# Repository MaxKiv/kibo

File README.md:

# The KiBo splitboard

An awesome custom split keyboard, at least I think so 😉. Made by Max Kivits and
Timon Borg, the KiBo!

This keyboard is loosely based on the [Piantor] and [Cantor] keyboards. It's a
42-key diodeless non-flippable cherry-mx hotswapable mechanical split keyboard
with aggressive column staggering. It's powered by 2 RP2040, completely overkill!
I redesigned the PCB to use cherry-mx style hotswap switches and adjusted the
margins so it fits my hands better.
The pcb features an artsy silklayer, because why not?

The casing is designed by Timon Borg, a god amongst fusion360 users!

KiBo uses the amazing [qmk] firmware to become a keyboard.

## Features

* RP2040 MCU - A low-cost, easy-to-source, powerful microcontroller with dual Arm Cortex-M0+ @ 133MHz, 264kB on-chip SRAM and 2MB (up to 16MB, depending on the breakout board) off-chip external flash memory. You can enable a lot of features and layers. Never worry about the firmware size limit.
* Cantor layout - Ergonomic strong column staggering for short pinkies.
* Non-flippable PCBs - Fewer ways to make mistakes when you install the controller breakout boards. Great for first time keyboard builders.
* Diodeless - A more robust build with fewer things to solder or break.
* Hybrid hotswap and soldered-in low profile choc switches - Experiment with different key switches with the hotswap sockets, or solder the key switches for a more stable build.
* Breakable pinky column - Easily convert the PCB from a 42-key to 36-key layout. You can snap off the pinky column without specialized tools.

## Bill of Materials (BOM)

Quantity | Item | Notes
--- | --- | ---
1 | KiBo PCB (Left)
1 | KiBo PCB (Right)
2 | RP2040 breakout boards (such as Raspberry Pi Pico or WeAct RP2040)
42 (or 36) | cherry-mx style switches of your favorite flavor
42 (or 36) | cherry-mx style keycaps of your favorite variety
2 | TRRS jack (PJ-320A)
1 | 3.5mm TRRS cable | TRS cable cannot be used
42 (or 36) | cherry-mx style hotswap sockets | Optional, you can solder the switches directly if you do not use hotswap sockets
4 | Pin headers (20p) or sockets  | Only required for boards without castellated holes
2 | 10kΩ 1206 (3216M) SMD resistor | Only required if you do not want to use SPLIT_USB DETECT, and for boards without a built in VBUS_SENSE circuit
2 | 5.6kΩ 1206 (3216M) SMD resistor | Only required if you do not want to use SPLIT_USB DETECT, and for boards without a built in VBUS_SENSE circuit
1 | KiBo Case (Left) | 3D print your own
1 | KiBo Case (Right)| 3D print your own

* Note: Raspberry Pi Pico comes with castellated holes and a built in VBUS_SENSE circuit

[Piantor]: https://github.com/beekeeb/piantor
[Cantor]: https://github.com/diepala/cantor
[qmk]: https://github.com/qmk/qmk_firmware

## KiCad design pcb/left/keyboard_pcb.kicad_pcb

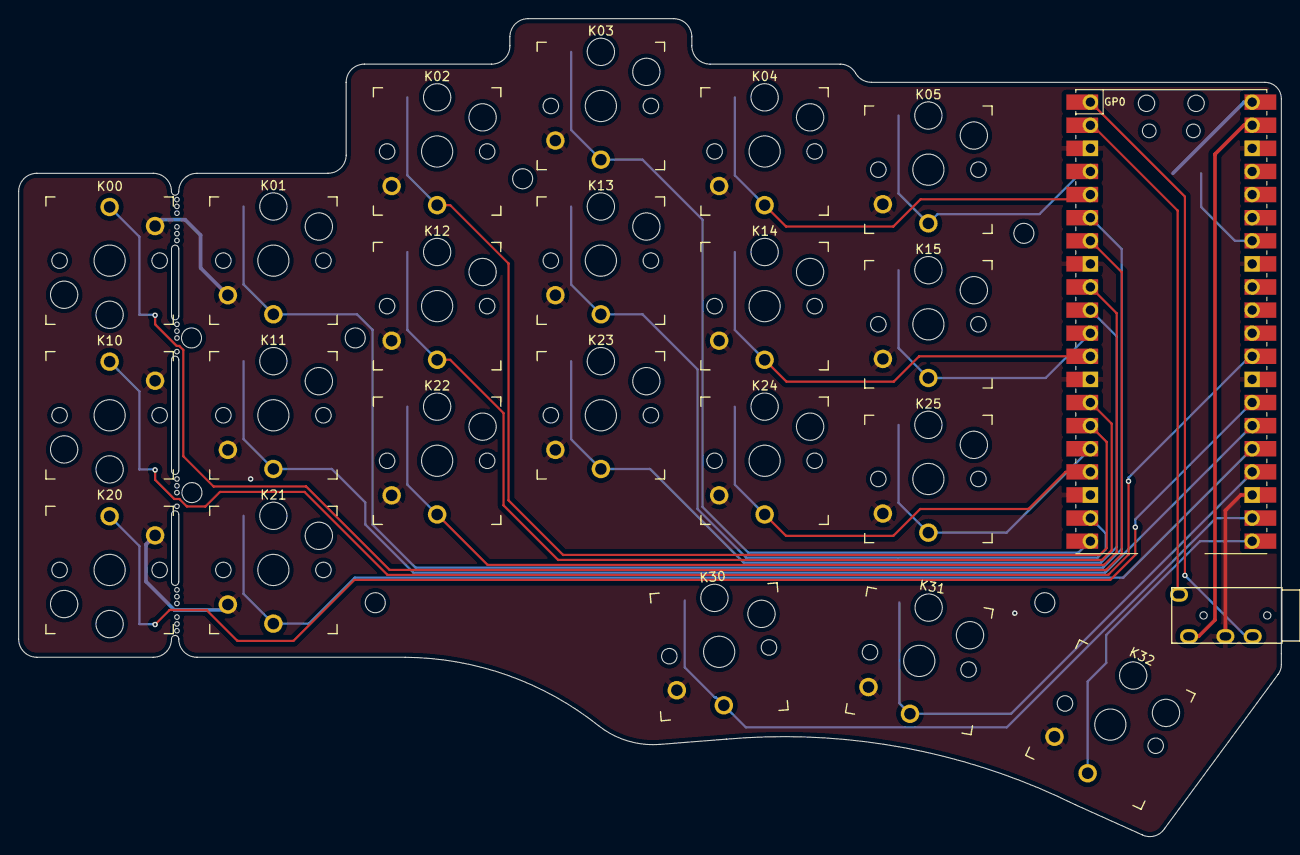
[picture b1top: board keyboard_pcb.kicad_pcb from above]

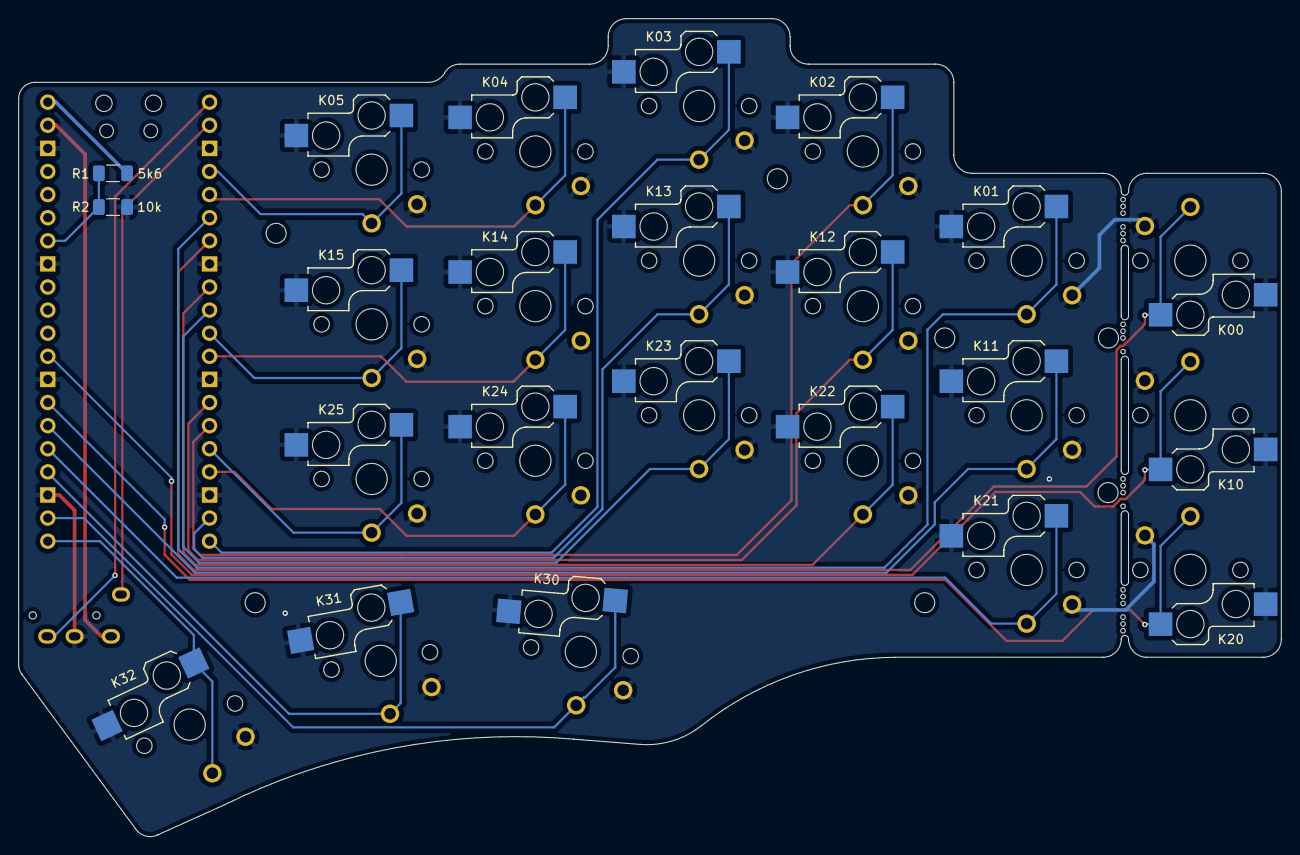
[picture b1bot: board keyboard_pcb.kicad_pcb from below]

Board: 2 copper layers, 138.8 x 89.9 mm, 36 parts (2 on the bottom side), 27 nets.

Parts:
H1, H1#2, H2, H3, H4, H4#2, H4#3: MountingHole; MountingHole_2.2mm_M2-8mm
J1: TRRS; TRRS-PJ-320A
K00, K01, K02, K03, K04, K05, K10, K11, K12, K13, K14, K15, K20, K21, K22, K23, K24, K25, K30, K31, K32: KEYSW; Kailh_socket_PG1350_optional
MB1, MB2: MountingHole; mousebites_2
MB3, MB4: MountingHole; mousebites_3
R1: 5k6; R_1206_3216Metric_Pad1.30x1.75mm_HandSolder
R2: 10k; R_1206_3216Metric_Pad1.30x1.75mm_HandSolder
U2: Pico; RPi_Pico_SMD_TH

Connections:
/k00: K00.1, U2.7 (GPIO5)
/k01: K01.1, U2.6 (GPIO4)
/k02: K02.1, U2.15 (GPIO11)
/k03: K03.1, U2.20 (GPIO15)
/k04: K04.1, U2.5 (GPIO3)
/k05: K05.1, U2.4 (GPIO2)
/k10: K10.1, U2.29 (GPIO22)
/k11: K11.1, U2.26 (GPIO20)
/k12: K12.1, U2.14 (GPIO10)
/k13: K13.1, U2.19 (GPIO14)
/k14: K14.1, U2.12 (GPIO9)
/k15: K15.1, U2.11 (GPIO8)
/k20: K20.1, U2.27 (GPIO21)
/k21: K21.1, U2.25 (GPIO19)
/k22: K22.1, U2.9 (GPIO6)
/k23: K23.1, U2.10 (GPIO7)
/k24: K24.1, U2.17 (GPIO13)
/k25: K25.1, U2.16 (GPIO12)
/k30: K30.1, U2.22 (GPIO17)
/k31: K31.1, U2.24 (GPIO18)
/k32: K32.1, U2.21 (GPIO16)
GND: J1.3 (RING1), K00.2, K01.2, K02.2, K03.2, K04.2, K05.2, K10.2, K11.2, K12.2, K13.2, K14.2, K15.2, K20.2, K21.2, K22.2, K23.2, K24.2, K25.2, K30.2, K31.2, K32.2, R2.2, U2.3 (GND), U2.8 (GND), U2.13 (GND), U2.18 (GND), U2.23 (GND), U2.28 (GND), U2.33 (AGND), U2.38 (GND)
VBUS: R1.1, U2.40 (VBUS)
VCC: J1.2 (TIP), U2.39 (VSYS)
rx: J1.1 (SLEEVE), U2.2 (GPIO1)
tx: J1.4 (RING2), U2.1 (GPIO0)
vbus_sense: R1.2, R2.1, U2.34 (GPIO28_ADC2)

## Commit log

2023-08-23 feat: new keyboard!
2023-08-23 feat: update readme banner
2023-08-23 feat: right keyboard, silkscreen
2023-09-23 nice commit msg
2023-09-23 cleanup
2024-12-30 chore: update readme
2025-03-25 feat(nix): add nix devshell

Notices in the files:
README.md:
License: GPL v3
